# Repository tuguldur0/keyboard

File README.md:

# keyboard
custom keyboard made for and with the help of Keeb YSWS by Hack Club

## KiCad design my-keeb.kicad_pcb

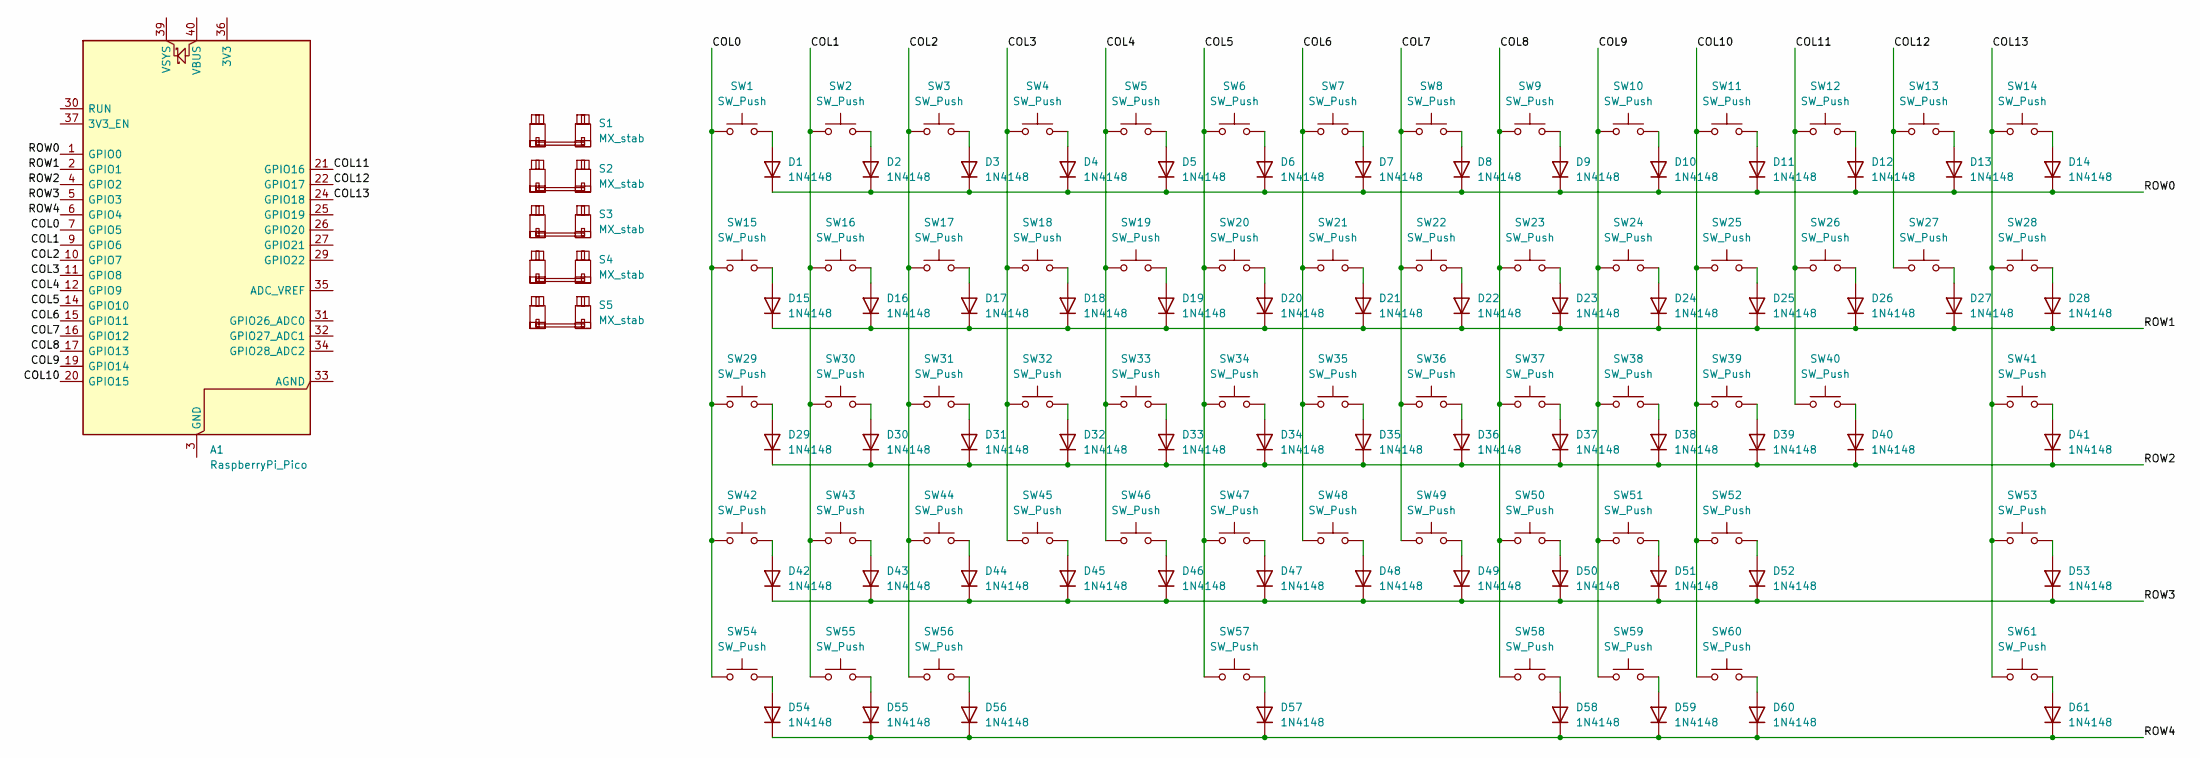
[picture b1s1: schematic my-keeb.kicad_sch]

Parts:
A1: RaspberryPi_Pico; RaspberryPi_Pico_Common_THT
D1, D2, D3, D4, D5, D6, D7, D8, D9, D10, D11, D12, D13, D14, D15, D16, D17, D18, D19, D20, D21, D22, D23, D24, D25, D26, D27, D28, D29, D30, D31, D32, D33, D34, D35, D36, D37, D38, D39, D40, D41, D42, D43, D44, D45, D46, D47, D48, D49, D50, D51, D52, D53, D54, D55, D56, D57, D58, D59, D60, D61: 1N4148; D_DO-35_SOD27_P7.62mm_Horizontal
S1: MX_stab; STAB_MX_2u
S2, S3: MX_stab; STAB_MX_2.25u
S4: MX_stab; STAB_MX_2.75u
S5: MX_stab; STAB_MX_6.25u
SW1, SW2, SW3, SW4, SW5, SW6, SW7, SW8, SW9, SW10, SW11, SW12, SW13, SW14, SW16, SW17, SW18, SW19, SW20, SW21, SW22, SW23, SW24, SW25, SW26, SW27, SW30, SW31, SW32, SW33, SW34, SW35, SW36, SW37, SW38, SW39, SW40, SW41, SW42, SW43, SW44, SW45, SW46, SW47, SW48, SW49, SW50, SW51, SW52, SW53, SW57: SW_Push; SW_MX_1u
SW15, SW28: SW_Push; SW_MX_1.5u
SW29: SW_Push; SW_MX_1.75u
SW54, SW55, SW56, SW58, SW59, SW60, SW61: SW_Push; SW_MX_1.25u

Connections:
/COL0: A1.7 (GPIO5), SW1.1, SW15.1, SW29.1, SW42.1, SW54.1
/COL1: A1.9 (GPIO6), SW2.1, SW16.1, SW30.1, SW43.1, SW55.1
/COL2: A1.10 (GPIO7), SW3.1, SW17.1, SW31.1, SW44.1, SW56.1
/COL3: A1.11 (GPIO8), SW4.1, SW18.1, SW32.1, SW45.1
/COL4: A1.12 (GPIO9), SW5.1, SW19.1, SW33.1, SW46.1
/COL5: A1.14 (GPIO10), SW6.1, SW20.1, SW34.1, SW47.1, SW57.1
/COL6: A1.15 (GPIO11), SW7.1, SW21.1, SW35.1, SW48.1
/COL7: A1.16 (GPIO12), SW8.1, SW22.1, SW36.1, SW49.1
/COL8: A1.17 (GPIO13), SW9.1, SW23.1, SW37.1, SW50.1, SW58.1
/COL9: A1.19 (GPIO14), SW10.1, SW24.1, SW38.1, SW51.1, SW59.1
/COL10: A1.20 (GPIO15), SW11.1, SW25.1, SW39.1, SW52.1, SW60.1
/COL11: A1.21 (GPIO16), SW12.1, SW26.1, SW40.1
/COL12: A1.22 (GPIO17), SW13.1, SW27.1
/COL13: A1.24 (GPIO18), SW14.1, SW28.1, SW41.1, SW53.1, SW61.1
/ROW0: A1.1 (GPIO0), D1.1 (K), D2.1 (K), D3.1 (K), D4.1 (K), D5.1 (K), D6.1 (K), D7.1 (K), D8.1 (K), D9.1 (K), D10.1 (K), D11.1 (K), D12.1 (K), D13.1 (K), D14.1 (K)
/ROW1: A1.2 (GPIO1), D15.1 (K), D16.1 (K), D17.1 (K), D18.1 (K), D19.1 (K), D20.1 (K), D21.1 (K), D22.1 (K), D23.1 (K), D24.1 (K), D25.1 (K), D26.1 (K), D27.1 (K), D28.1 (K)
/ROW2: A1.4 (GPIO2), D29.1 (K), D30.1 (K), D31.1 (K), D32.1 (K), D33.1 (K), D34.1 (K), D35.1 (K), D36.1 (K), D37.1 (K), D38.1 (K), D39.1 (K), D40.1 (K), D41.1 (K)
/ROW3: A1.5 (GPIO3), D42.1 (K), D43.1 (K), D44.1 (K), D45.1 (K), D46.1 (K), D47.1 (K), D48.1 (K), D49.1 (K), D50.1 (K), D51.1 (K), D52.1 (K), D53.1 (K)
/ROW4: A1.6 (GPIO4), D54.1 (K), D55.1 (K), D56.1 (K), D57.1 (K), D58.1 (K), D59.1 (K), D60.1 (K), D61.1 (K)
unnamed: A1.3 (GND), A1.8 (GND), A1.13 (GND), A1.18 (GND), A1.23 (GND), A1.28 (GND), A1.38 (GND)
unnamed: D1.2 (A), SW1.2
unnamed: D2.2 (A), SW2.2
unnamed: D3.2 (A), SW3.2
unnamed: D4.2 (A), SW4.2
unnamed: D5.2 (A), SW5.2
unnamed: D6.2 (A), SW6.2
unnamed: D7.2 (A), SW7.2
unnamed: D8.2 (A), SW8.2
unnamed: D9.2 (A), SW9.2
unnamed: D10.2 (A), SW10.2
unnamed: D11.2 (A), SW11.2
unnamed: D12.2 (A), SW12.2
unnamed: D13.2 (A), SW13.2
unnamed: D14.2 (A), SW14.2
unnamed: D15.2 (A), SW15.2
unnamed: D16.2 (A), SW16.2
unnamed: D17.2 (A), SW17.2
unnamed: D18.2 (A), SW18.2
unnamed: D19.2 (A), SW19.2
unnamed: D20.2 (A), SW20.2
unnamed: D21.2 (A), SW21.2
unnamed: D22.2 (A), SW22.2
unnamed: D23.2 (A), SW23.2
unnamed: D24.2 (A), SW24.2
unnamed: D25.2 (A), SW25.2
unnamed: D26.2 (A), SW26.2
unnamed: D27.2 (A), SW27.2
unnamed: D28.2 (A), SW28.2
unnamed: D29.2 (A), SW29.2
unnamed: D30.2 (A), SW30.2
unnamed: D31.2 (A), SW31.2
unnamed: D32.2 (A), SW32.2
unnamed: D33.2 (A), SW33.2
unnamed: D34.2 (A), SW34.2
unnamed: D35.2 (A), SW35.2
unnamed: D36.2 (A), SW36.2
unnamed: D37.2 (A), SW37.2
unnamed: D38.2 (A), SW38.2
unnamed: D39.2 (A), SW39.2
unnamed: D40.2 (A), SW40.2
unnamed: D41.2 (A), SW41.2
unnamed: D42.2 (A), SW42.2
unnamed: D43.2 (A), SW43.2
unnamed: D44.2 (A), SW44.2
unnamed: D45.2 (A), SW45.2
unnamed: D46.2 (A), SW46.2
unnamed: D47.2 (A), SW47.2
unnamed: D48.2 (A), SW48.2
unnamed: D49.2 (A), SW49.2
unnamed: D50.2 (A), SW50.2
unnamed: D51.2 (A), SW51.2
unnamed: D52.2 (A), SW52.2
unnamed: D53.2 (A), SW53.2
unnamed: D54.2 (A), SW54.2
unnamed: D55.2 (A), SW55.2
unnamed: D56.2 (A), SW56.2
unnamed: D57.2 (A), SW57.2
unnamed: D58.2 (A), SW58.2
unnamed: D59.2 (A), SW59.2
unnamed: D60.2 (A), SW60.2
unnamed: D61.2 (A), SW61.2

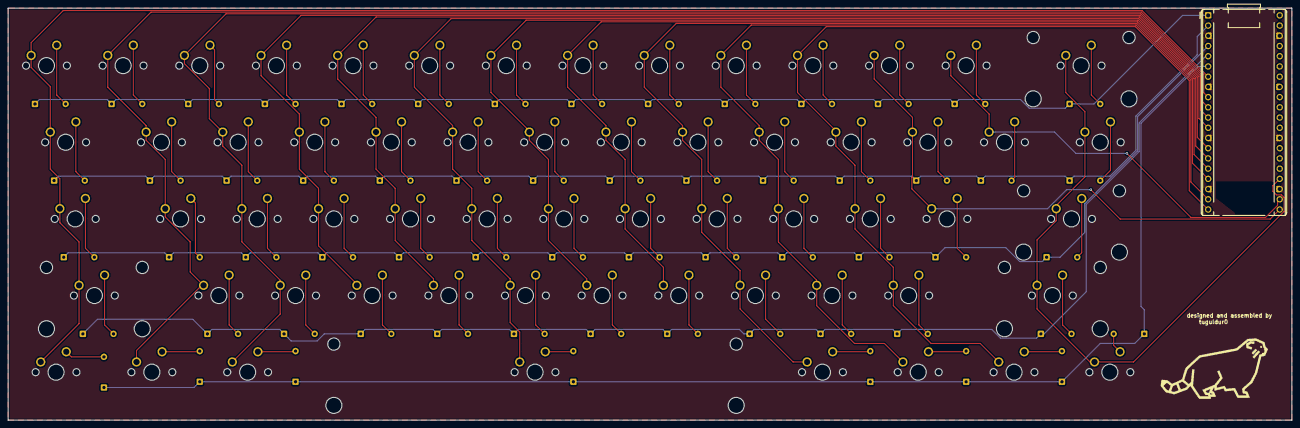
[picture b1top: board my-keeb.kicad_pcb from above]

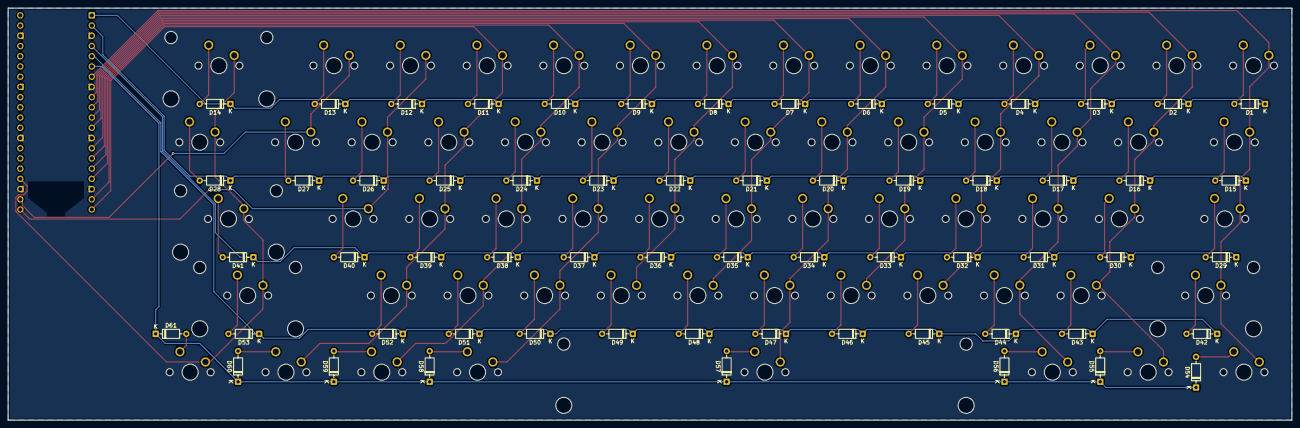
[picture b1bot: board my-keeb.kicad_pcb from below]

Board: 2 copper layers, 319.1 x 102.4 mm, 128 parts (61 on the bottom side), 81 nets.
